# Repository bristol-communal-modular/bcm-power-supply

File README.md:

# BCM Power Supply

A basic eurorack power supply that can provide +12v, -12v, and +5v, at up to 1 Amp on each.

There are three PCBs here :-

* A power supply, that takes +15 volts and outputs +12v, -12v and +5v onto two eurorack power connectors
* A front panel that a DC jack and power indicator board can be mounted on
* A power indicator board that has LEDs for the three voltage rails

The power board is designed with four M3 holes in the corners, so it can be mounted into a case using stand-offs.

## Contact

Come down the Bristol Hackspace on a Tuesday night to say hello.

## License

This project is shared under an [Attribution-NonCommercial-ShareAlike 4.0 International License](https://creativecommons.org/licenses/by-nc-sa/4.0/)

This means that you can share the info here around, and transform or build upon the circuits and designs in here, as long as you share anything you do under the same license and give BCM a shout-out.

We don't license this for commercial purposes, but if you'd like to run a workshop with this or some variation of it, just get in contact and we can sort something out.
If you want to build a couple to sell to your mates then we're pretty fine with that as well.

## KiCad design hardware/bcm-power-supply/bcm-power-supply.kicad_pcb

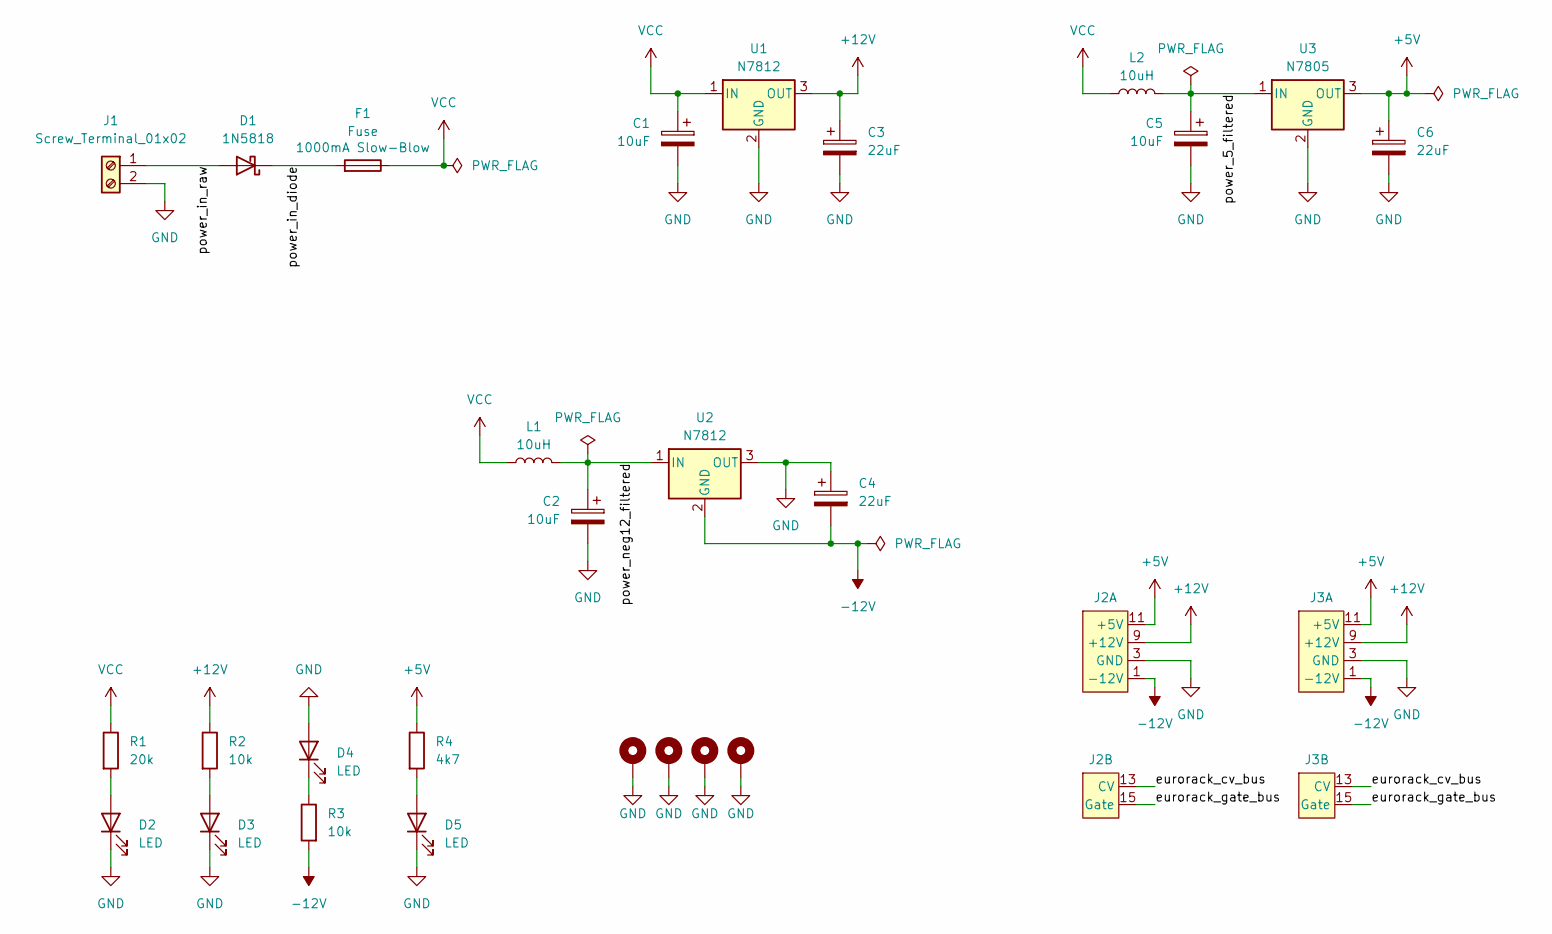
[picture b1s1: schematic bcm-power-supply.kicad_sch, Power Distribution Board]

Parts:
C1, C2, C5: 10uF; CP_Radial_D6.3mm_P2.50mm; Voltage 50V
C3, C4, C6: 22uF; CP_Radial_D6.3mm_P2.50mm; Voltage 50V
D1: 1N5818; D_DO-41_SOD81_P10.16mm_Horizontal
D2, D3, D4, D5: LED; LED_D3.0mm
F1: Fuse; Fuseholder_Clip-5x20mm_Littelfuse_520_Inline_P20.50x5.80mm_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
H1, H2, H3, H4: MountingHole_Pad; MountingHole_3.2mm_M3_DIN965_Pad
J1: Screw_Terminal_01x02; TerminalBlock_Phoenix_MKDS-1,5-2-5.08_1x02_P5.08mm_Horizont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; MPN 1715022
J2, J3: Conn_02x08_Odd_Even; Eurorack_Power_IDC-Header_2x08_P2.54mm_Vertical
L1, L2: 10uH; L_Toroid_Vertical_L10.0mm_W5.0mm_P5.08mm; MPN SN3-200
R1: 20k; R_Axial_DIN0207_L6.3mm_D2.5mm_P10.16mm_Horizontal; Tolerance 1%
R2, R3: 10k; R_Axial_DIN0207_L6.3mm_D2.5mm_P10.16mm_Horizontal; Tolerance 1%
R4: 4k7; R_Axial_DIN0207_L6.3mm_D2.5mm_P10.16mm_Horizontal; Tolerance 1%
U1, U2: N7812; TO-220-3_Horizontal_TabDown
U3: N7805; TO-220-3_Horizontal_TabDown

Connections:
+5V: C6.1, J2.11 (+5V), J2.12 (+5V), J3.11 (+5V), J3.12 (+5V), R4.1, U3.3 (OUT)
+12V: C3.1, J2.9 (+12V), J2.10 (+12V), J3.9 (+12V), J3.10 (+12V), R2.1, U1.3 (OUT)
-12V: C4.2, J2.1 (-12V), J2.2 (-12V), J3.1 (-12V), J3.2 (-12V), R3.2, U2.2 (GND)
/eurorack_cv_bus: J2.13 (CV), J2.14 (CV), J3.13 (CV), J3.14 (CV)
/eurorack_gate_bus: J2.15 (Gate), J2.16 (Gate), J3.15 (Gate), J3.16 (Gate)
/power_5_filtered: C5.1, L2.2, U3.1 (IN)
/power_in_diode: D1.1 (K), F1.2
/power_in_raw: D1.2 (A), J1.1
/power_neg12_filtered: C2.1, L1.2, U2.1 (IN)
GND: C1.2, C2.2, C3.2, C4.1, C5.2, C6.2, D2.1 (K), D3.1 (K), D4.2 (A), D5.1 (K), H1.1, H2.1, H3.1, H4.1, J1.2, J2.3 (GND), J2.4 (GND), J2.5 (GND), J2.6 (GND), J2.7 (GND), J2.8 (GND), J3.3 (GND), J3.4 (GND), J3.5 (GND), J3.6 (GND), J3.7 (GND), J3.8 (GND), U1.2 (GND), U2.3 (OUT), U3.2 (GND)
unnamed: D2.2 (A), R1.2
unnamed: D3.2 (A), R2.2
unnamed: D4.1 (K), R3.1
unnamed: D5.2 (A), R4.2
VCC: C1.1, F1.1, L1.1, L2.1, R1.1, U1.1 (IN)

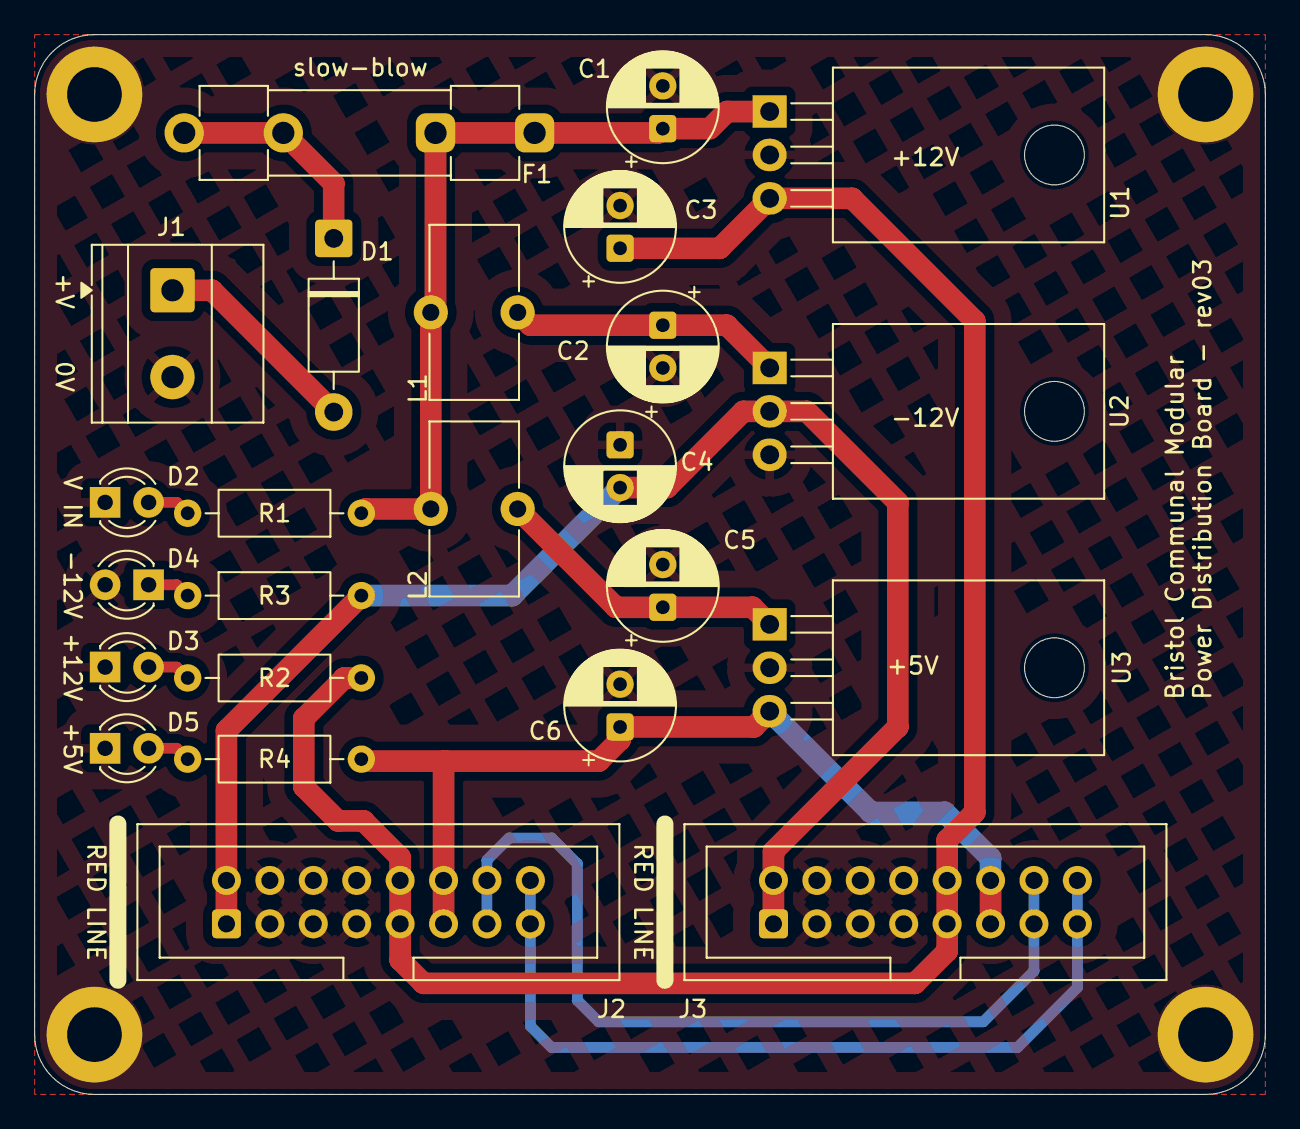
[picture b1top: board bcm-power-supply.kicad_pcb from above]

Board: 2 copper layers, 72.0 x 62.0 mm, 29 parts (1 on the bottom side), 15 nets.

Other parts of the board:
Ref**: Val**; BCM_Logo_small_15mmx15mm

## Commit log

2026-01-03 Updating with 5v output
    And making the board smaller
2026-01-03 Moving gerber files
2026-01-03 Adding input panel
2026-01-24 Updating power supply board to give more space for regulators
2026-01-24 Adding build info
2026-01-24 Updating README

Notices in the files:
hardware/bcm-power-supply/bcm-power-supply.kicad_pcb:
creativecommons.org/licenses/by/4.0
License: CC BY 4.0
